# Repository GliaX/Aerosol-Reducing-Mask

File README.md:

November 27, 2020

# Suspension of Marketing and Sales of the Aerosol-Reducing-Mask (ARM)

Effective November 27 (2020), the ARM team is suspending any sales or distribution of the current version of the ARM.

Review of clinical trial data that became available to the team on November 26  shows that the ARM device is not as effective at reducing leak and aerosolization as earlier data had suggested. The [preliminary data and analysis report](https://github.com/GliaX/Aerosol-Reducing-Mask/blob/master/reports/20201210%20Clinical%20Trial%20Summary%20Leak%20Data.md) is posted to the repository.

The clinical trial was not a requirement for regulatory approval from Health Canada and the device is still approved under an Interim Order. However the trial data suggests that while safe and effective at providing respiratory support, the device fails to meets its primary indication (protection of health care providers and other patients from infectious aerosols), we are withholding all sales and deployments of the device.

We are currently undertaking a detailed analysis of the device and causes of failure in order to create a road map for required modifications for a subsequent version. Such modifications and the necessary testing will likely not be completed in sufficient time to meet current urgent needs. All analysis reports and other documents will continue to be posted on the public repository.

# Aerosol Reducing Mask for Non-Invasive Ventilation

## Purpose
The Minimizing Aerosolization In Non-invasive (MAIN) Ventilation COVID-19 mask
is a sealed, filtered, full-face mask minimizing virus aerosolization and
enabling the use of Non-Invasive Positive Pressure Ventilation (NIPPV) machines
for patients with COVID-19, or similar symptoms.  The mask adaptor is the
primary connection between the sealed facemask and standard medical 22mm
respiratory tubing, fittings and filters. An additive manufacturing method, also
known as 3D printing, was used to produce the mask adapter because of its
relative speed to make objects of complicated geometries and availability. Due
to the medical nature of the adapter, certain specifications must be followed in
its production to prevent any infectious transmission from the patient to health
care workers and other patients.

## Bill Of Materials
 * [3M Scott AV-2000 Facepiece](https://www.3mscott.com/products/av-2000-facepiece/)
 * 3M Gasket seal
 * 3D printed adapter (ABS)
 * Safety release strap, 25mm width x 35cm length[[MEC](https://www.mec.ca/en/product/5020-829/1%22%2825mm%29-Nylon-Tubular-Climbing-Webbing)]

## Adaptor 3D Printing Specifications and Parameters

 * Adapter Version: v1.0
 * Filament Material: ABS
 * Printer Nozzle: 0.4mm
 * Infill Percentage & Pattern: 100% Infill, Rectilinear infill
 * Wall thickness: 2.0mm (5 wall/perimeters with 0.4mm nozzle)
 * Top and bottom thickness: 2.0mm (5 top and bottom layers at 0.2mm layer height)
 * Supports: Required
 * Raft: Not preferred; Printing on the bed creates a smoother finish
 * Orientation: Mask face on the bed, Outer face upwards (See Figure 1)

Additional Slicer Settings:
 * Use ‘random start points for all perimeters’ (Cura)
 * Use ‘Connect infill lines’ (Cura)
 * Use ‘Random start points for all perimeters’ (Simply3D)

*Figure 1: Orientation of Adapter v1.0 on Print Bed*

* NOTE: ABS is prone to thermoplastic contraction (shrinkage). If the slicing
software does not already compensate for this shrinkage, consider measuring the
product to ensure the correct scale. Amount of contraction can vary between
different brands of ABS – printing calibration tools and test-prints recommended
to determine exact percentage to scale.

## Post-Print Check Guidelines
Ensure the following:
 * Inside diameter of female port on outward face should measure between 22.37
 +0.1/-0.15mm on outside face (see Figure 2). Use of digital calipers strongly
 recommended.
 * Note tolerances for other dimensions post printing (also see Figure 2).
 * Layers adhere properly to each other
 * Walls are completely fused together
 * Surfaces (outer and inner) are smooth without gaps, burrs, blobs
 * The print has decent flexibility (i.e. latch)

*Figure 2: Critical part dimensions*

# Print Traceability Guidelines

For each batch printed, the following items must be logged:
 * Material used
 * Lot number of material used
 * Colour of material
 * Date of print
 * Machines used for print
 
# Attaching safety release
 
 * Insert strap into bottom right buckle of helmet - Patient should be able to pull strap with right hand.
 * Loop strap back approximately 6 cm.
 * Sew firmly using 3 runs across the area to sew.

*Figure 3: Front view of helmet*

*Figure 4: Strap inserted into buckle*

*Figure 5: Completed sewn strap*

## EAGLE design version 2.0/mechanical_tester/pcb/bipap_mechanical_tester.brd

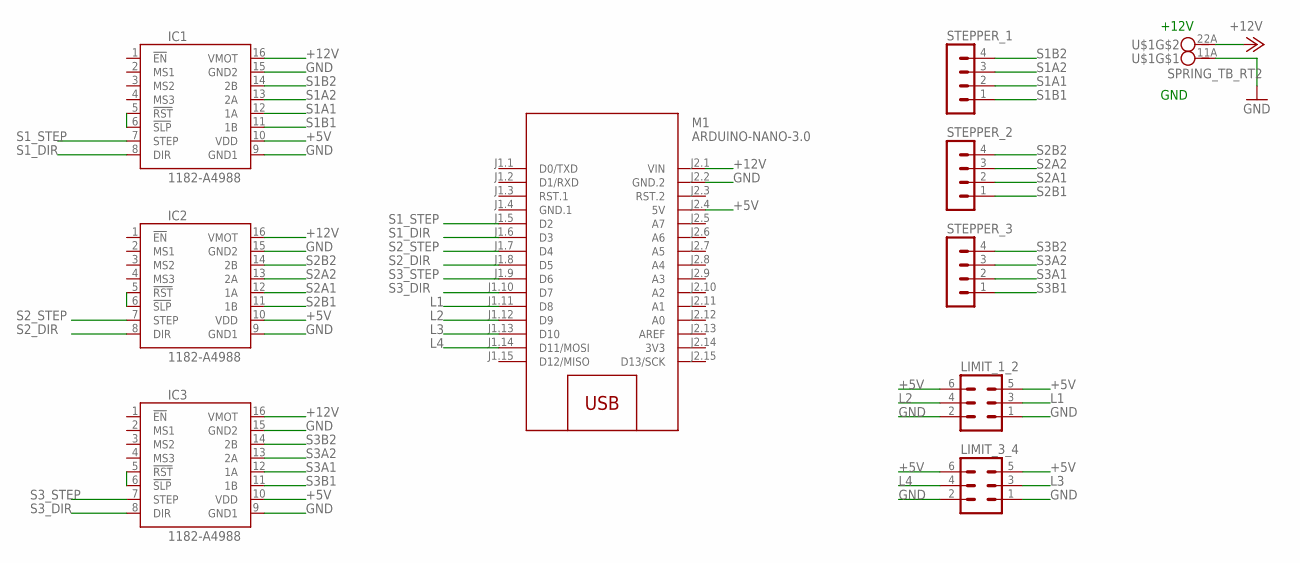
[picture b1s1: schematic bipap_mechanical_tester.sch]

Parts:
IC1, IC2, IC3: 1182-A4988; A4988
LIMIT_1_2, LIMIT_3_4: MA03-2
M1: ARDUINO-NANO-3.0
STEPPER_1, STEPPER_2, STEPPER_3: MA04-1
U$1: SPRING_TB_RT2

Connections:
3V3: M1.J2.14 (3V3)
+5V: IC1.10 (VDD), IC2.10 (VDD), IC3.10 (VDD), LIMIT_1_2.5, LIMIT_1_2.6, LIMIT_3_4.5, LIMIT_3_4.6, M1.J2.4 (5V)
+12V: IC1.16 (VMOT), IC2.16 (VMOT), IC3.16 (VMOT), M1.J2.1 (VIN), U$1.2A (2)
GND: IC1.9 (GND1), IC1.15 (GND2), IC2.9 (GND1), IC2.15 (GND2), IC3.9 (GND1), IC3.15 (GND2), LIMIT_1_2.1, LIMIT_1_2.2, LIMIT_3_4.1, LIMIT_3_4.2, M1.J2.2 (GND.2), U$1.1A (2)
GND.1: M1.J1.4 (GND.1)
L1: LIMIT_1_2.3, M1.J1.11 (D8)
L2: LIMIT_1_2.4, M1.J1.12 (D9)
L3: LIMIT_3_4.3, M1.J1.13 (D10)
L4: LIMIT_3_4.4, M1.J1.14 (D11/MOSI)
unnamed: IC1.5 (!RST), IC1.6 (!SLP)
unnamed: IC2.5 (!RST), IC2.6 (!SLP)
unnamed: IC3.5 (!RST), IC3.6 (!SLP)
S1A1: IC1.12 (1A), STEPPER_1.2
S1A2: IC1.13 (2A), STEPPER_1.3
S1B1: IC1.11 (1B), STEPPER_1.1
S1B2: IC1.14 (2B), STEPPER_1.4
S1_DIR: IC1.8 (DIR), M1.J1.6 (D3)
S1_STEP: IC1.7 (STEP), M1.J1.5 (D2)
S2A1: IC2.12 (1A), STEPPER_2.2
S2A2: IC2.13 (2A), STEPPER_2.3
S2B1: IC2.11 (1B), STEPPER_2.1
S2B2: IC2.14 (2B), STEPPER_2.4
S2_DIR: IC2.8 (DIR), M1.J1.8 (D5)
S2_STEP: IC2.7 (STEP), M1.J1.7 (D4)
S3A1: IC3.12 (1A), STEPPER_3.2
S3A2: IC3.13 (2A), STEPPER_3.3
S3B1: IC3.11 (1B), STEPPER_3.1
S3B2: IC3.14 (2B), STEPPER_3.4
S3_DIR: IC3.8 (DIR), M1.J1.10 (D7)
S3_STEP: IC3.7 (STEP), M1.J1.9 (D6)

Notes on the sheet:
+12V
GND

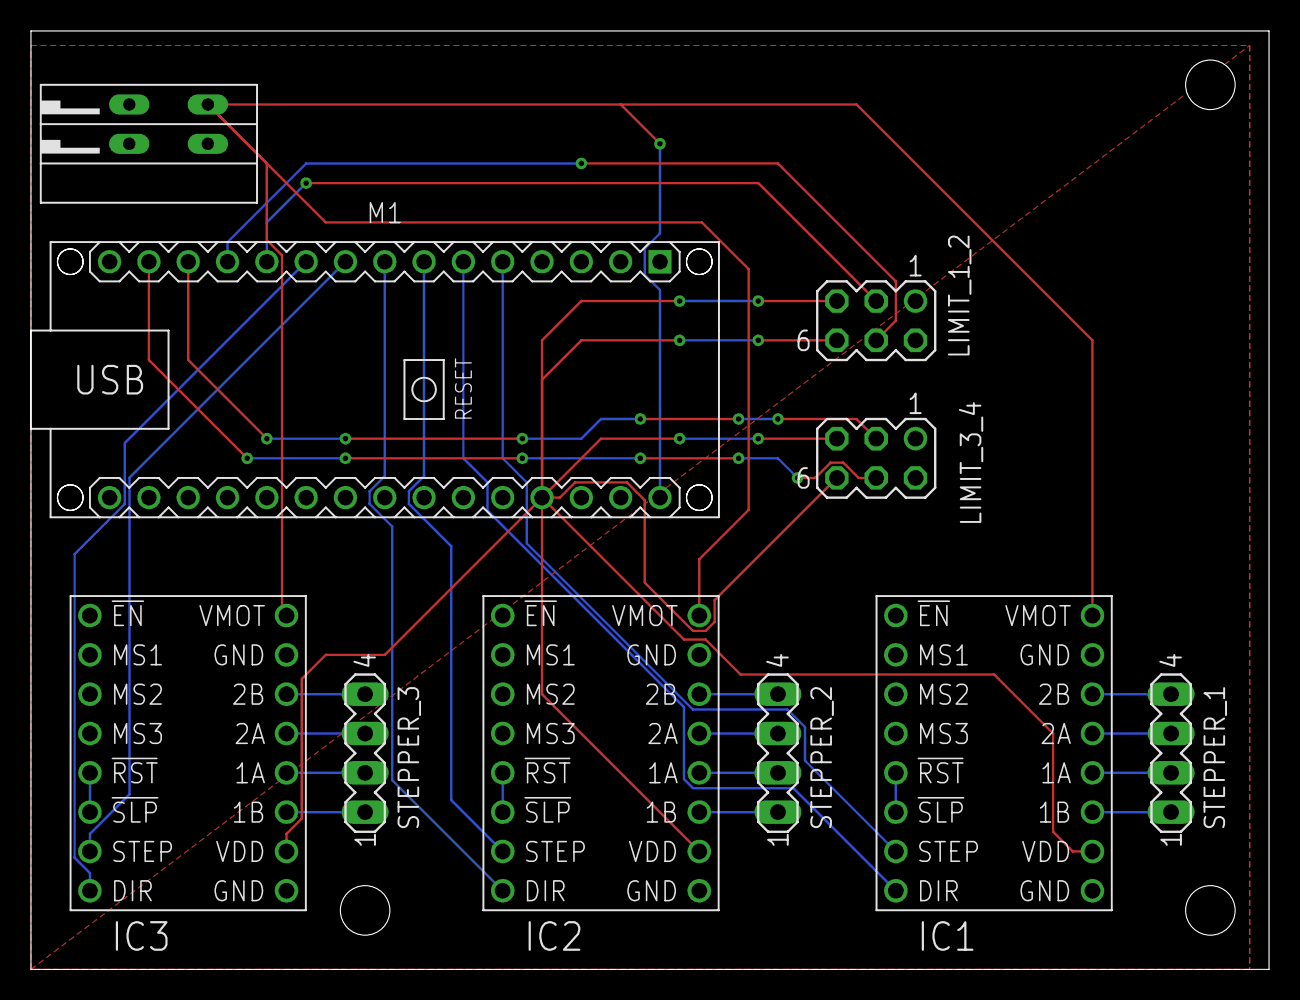
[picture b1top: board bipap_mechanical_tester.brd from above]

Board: 2 copper layers, 80.0 x 60.6 mm, 10 parts (0 on the bottom side), 28 nets.

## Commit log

2020-03-28 Add draft project plan by Wes
2020-04-02 Add and update planning documents
2020-04-02 Add research protocol for clinical trial
2020-04-06 Add clnical trial and ethics information
2020-04-08 Ethics revisions for HSREB
2020-04-08 Remove docx of LORA letter and add signed PDF
2020-04-12 Glia / GD Indemnification, signed
2020-04-12 Add GD ISO 9001
2020-04-12 Add instructions on downloading data from stellar
2020-04-12 Add whitepaper
2020-04-13 Add Adapter v1.0 STL
2020-04-14 Add device label
2020-04-18 Update ethics and clinical trial protocols as per most recent ethics
2020-04-18 Add gitignore
2020-04-21 Add Lawson Agreement
2020-04-21 Add how to process data
2020-04-22 Round of ethics request and response
2020-05-04 Add Interim order application
2020-05-06 Add communications with Health Canada
2020-05-13 Add interim order PDF
2020-05-13 Adapter 3MF
2020-05-13 Add readme
2020-05-13 Add media for README
2020-05-13 add captions
2020-05-13 Format caption
2020-05-13 Finish BOM
2020-05-15 Start quality assurance and add submersion testing
2020-05-15 Small formatting touchups to file
2020-05-15 Change bottom and top layers from 10 to 5
2020-05-15 Embiggened plate to provide more stability while gripping mesh
2020-05-15 Add gentle slope to top part so water doesn't stick there
2020-05-15 Move slots further out for more stability
2020-05-15 optimize print of top of rig, it needs to be printed at high infill,
2020-05-16 restore thickness to 5mm
2020-05-17 add post for preventing rotation
2020-05-17 add a slot for an elastic to the post
2020-05-19 add vent mesh
2020-05-20 increase diameter
2020-05-20 make posts longer, vent bigger, and add m5 jacket
2020-05-28 Updated bipap instructions
2020-05-28 Updated to Class 2
2020-05-28 Add ethics approval
2020-05-29 Adding Ethics Approval Letters
    for original and ammended application
2020-06-05 Modified device label for FDA compliance
2020-06-05 Add FDA-compliant english language manual
2020-11-11 Add strap instructions
2020-11-11 Formatting edit
2020-11-11 Formatting of images
2020-11-11 Revert "Formatting of images"
    This reverts commit 33b73b8a7b7a3b86bb786d5fd44ac903af22122e.
2020-11-12 Add link to edf2ascii
2020-12-04 Update README.md
    Adding Suspension Notice
2020-12-10 Create 20201210 Clinical Trial Summary Leak Data
2020-12-10 Initial Commit - Draft
2020-12-10 0.1
    Corrected Image Links
2020-12-10 0.11
2021-01-29 added model files for scuba adapters
2021-01-29 added images for the v2.0 connectors
2021-02-02 added f3d/f3z files
2021-02-05 added gcode and 3mf file for printing an expiratory and inspiratory port
2021-02-08 added mechanical fatigue tester design and electronics
2021-02-08 removed mechanical tester concept 1
2021-03-01 new version of expiratory port with larger lever arm for release
2021-04-29 added more material to expiratory port tabs and reduced height of expiratory port lever

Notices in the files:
parts and their libraries:
diy-modules: Released under the Creative Commons Attribution 4.0 International License: http://creativecommons.org/licenses/by/4.0
